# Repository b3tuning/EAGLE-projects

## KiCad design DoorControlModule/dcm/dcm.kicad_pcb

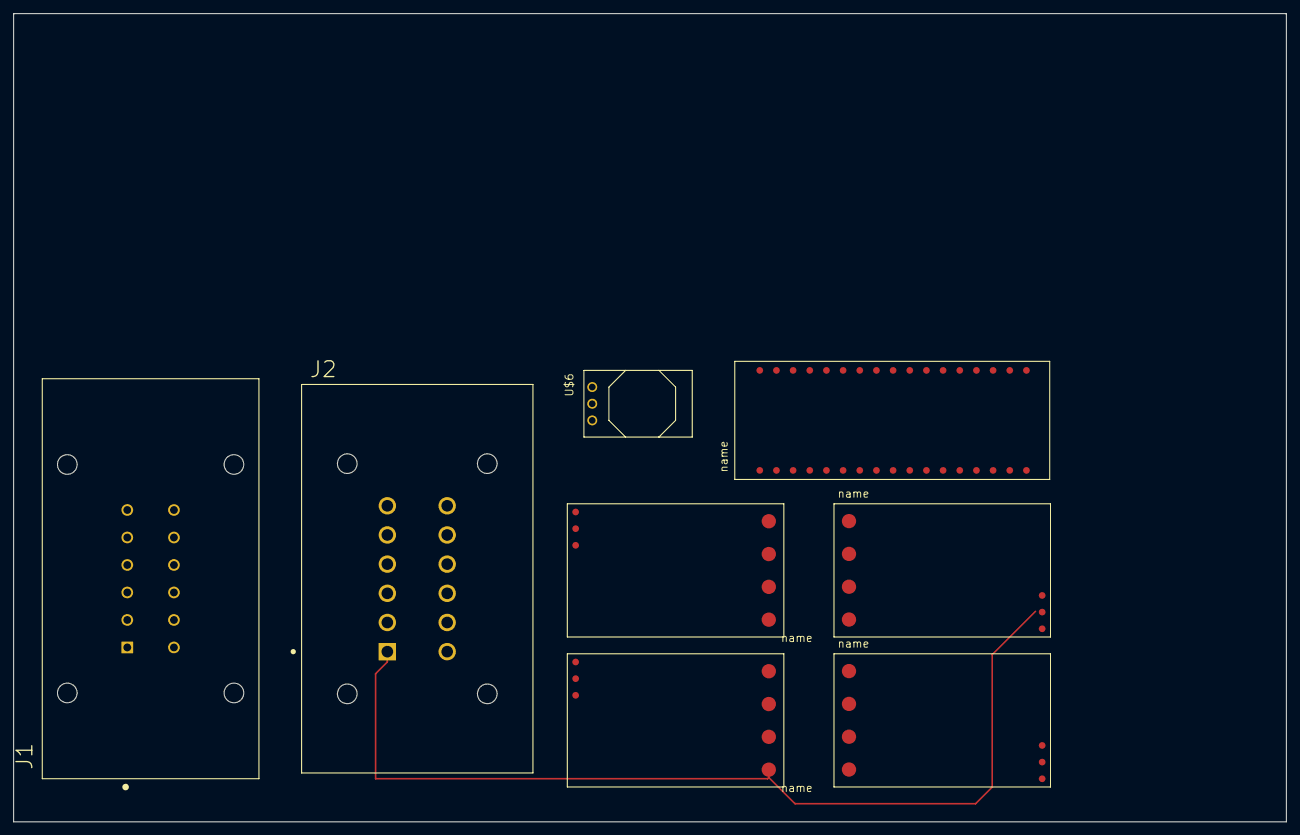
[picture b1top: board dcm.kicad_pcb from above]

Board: 2 copper layers, 194.0 x 123.2 mm, 8 parts (0 on the bottom side), 31 nets.

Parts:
J1: DTM15-12PA; TE_DTM15-12PA
J2: DT15-12PA; TE_DT15-12PA
U$1: WINDOW_MOTOR
U$2: MIRROR_V_MOTOR
U$3: MIRROR_H_MOTOR
U$4: FOLD_MOTOR
U$5: ARDUINO_MICRO
U$6: DCDC_OKI-78SR; OKI-78SRH

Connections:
unnamed: J2.1, U$1.VIN, U$2.VIN, U$3.VIN, U$4.VIN, U$6.1
unnamed: J2.12, U$1.GND, U$1.LGND, U$2.GND, U$2.LGND, U$3.GND, U$3.LGND, U$4.GND, U$4.LGND, U$5.LGND, U$6.2
unnamed: J2.3, U$1.OUTA
unnamed: J2.4, U$4.OUTA
unnamed: J2.5, U$3.OUTA
unnamed: J2.6, U$2.OUTA
unnamed: J2.7, U$2.OUTB
unnamed: J2.8, U$3.OUTB
unnamed: J2.9, U$4.OUTB
unnamed: J2.10, U$1.OUTB
unnamed: U$3.PWM, U$5.2/SDA
unnamed: U$3.DIR, U$5.3/SCL
unnamed: U$2.DIR, U$5.5(PWM)
unnamed: U$2.PWM, U$5.4(PWM)/A6
unnamed: U$4.PWM, U$5.6(PWM)/A7
unnamed: U$4.DIR, U$5.7
unnamed: U$1.PWM, U$5.8/A9
unnamed: U$1.DIR, U$5.9(PWM)/A10
unnamed: J1.1, U$5.1/TX
unnamed: J1.2, U$5.LGND2
unnamed: J1.3, U$5.11(PWM)
unnamed: J1.4, U$5.A2
unnamed: J1.5, U$5.A4
unnamed: J1.6, U$5.A1
unnamed: J1.7, U$5.A0
unnamed: J1.8, U$5.A5
unnamed: J1.9, U$5.A3
unnamed: U$5.+5V, U$6.3
unnamed: J1.10, U$5.10(PWM)/A11
unnamed: J1.11, U$5.12(PWM)/A12
unnamed: J1.12, U$5.0/RX

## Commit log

2019-07-10 adding DCM projects
2019-07-10 adding more DCM projects
2019-07-11 updating DCMv3
    x
2019-07-11 added current sense resistor
